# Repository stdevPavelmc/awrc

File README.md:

# Amateur Wireless Rotor Controller

An arduino based rotor controller connected via WiFi using the ESP8266 MCU

## Rationale

Why use cables when you have wifi around?

The hamlib project has a simple TCP daemon for abstract the rotor control, so we implemented the basic commands for that protocol and simulate a `rotctld` instance right on the rotor hardware; as today most of the softwares I use supports rotctld directly.

A web interface with position and simple commands is built on, I will improve it with time but this is low priority.

## How to compile

We use platformio, not the Arduino IDE, and main development is on linux (It must work on Windows/Mac), so you need Vscode/Codium and the Platformio addon.

By now I'm managing the dependencies as git submodules, so to install them you must do on the console this:

```sh
git clone https://github.com/stdevPavelmc/awrc.git
cd awrc
git submodule update
```

I will port them to platformio.ini deps in the future. Now just open the Platformio IDE and open the project and run. If you have internet plarformio will install the frameworks and tools for you.

## Hardware

There is a folder named `awrc-kicad` that has the project for board and schematics.

## This is a work in progress

Until labeled otherwise this project is an `alpha` code.

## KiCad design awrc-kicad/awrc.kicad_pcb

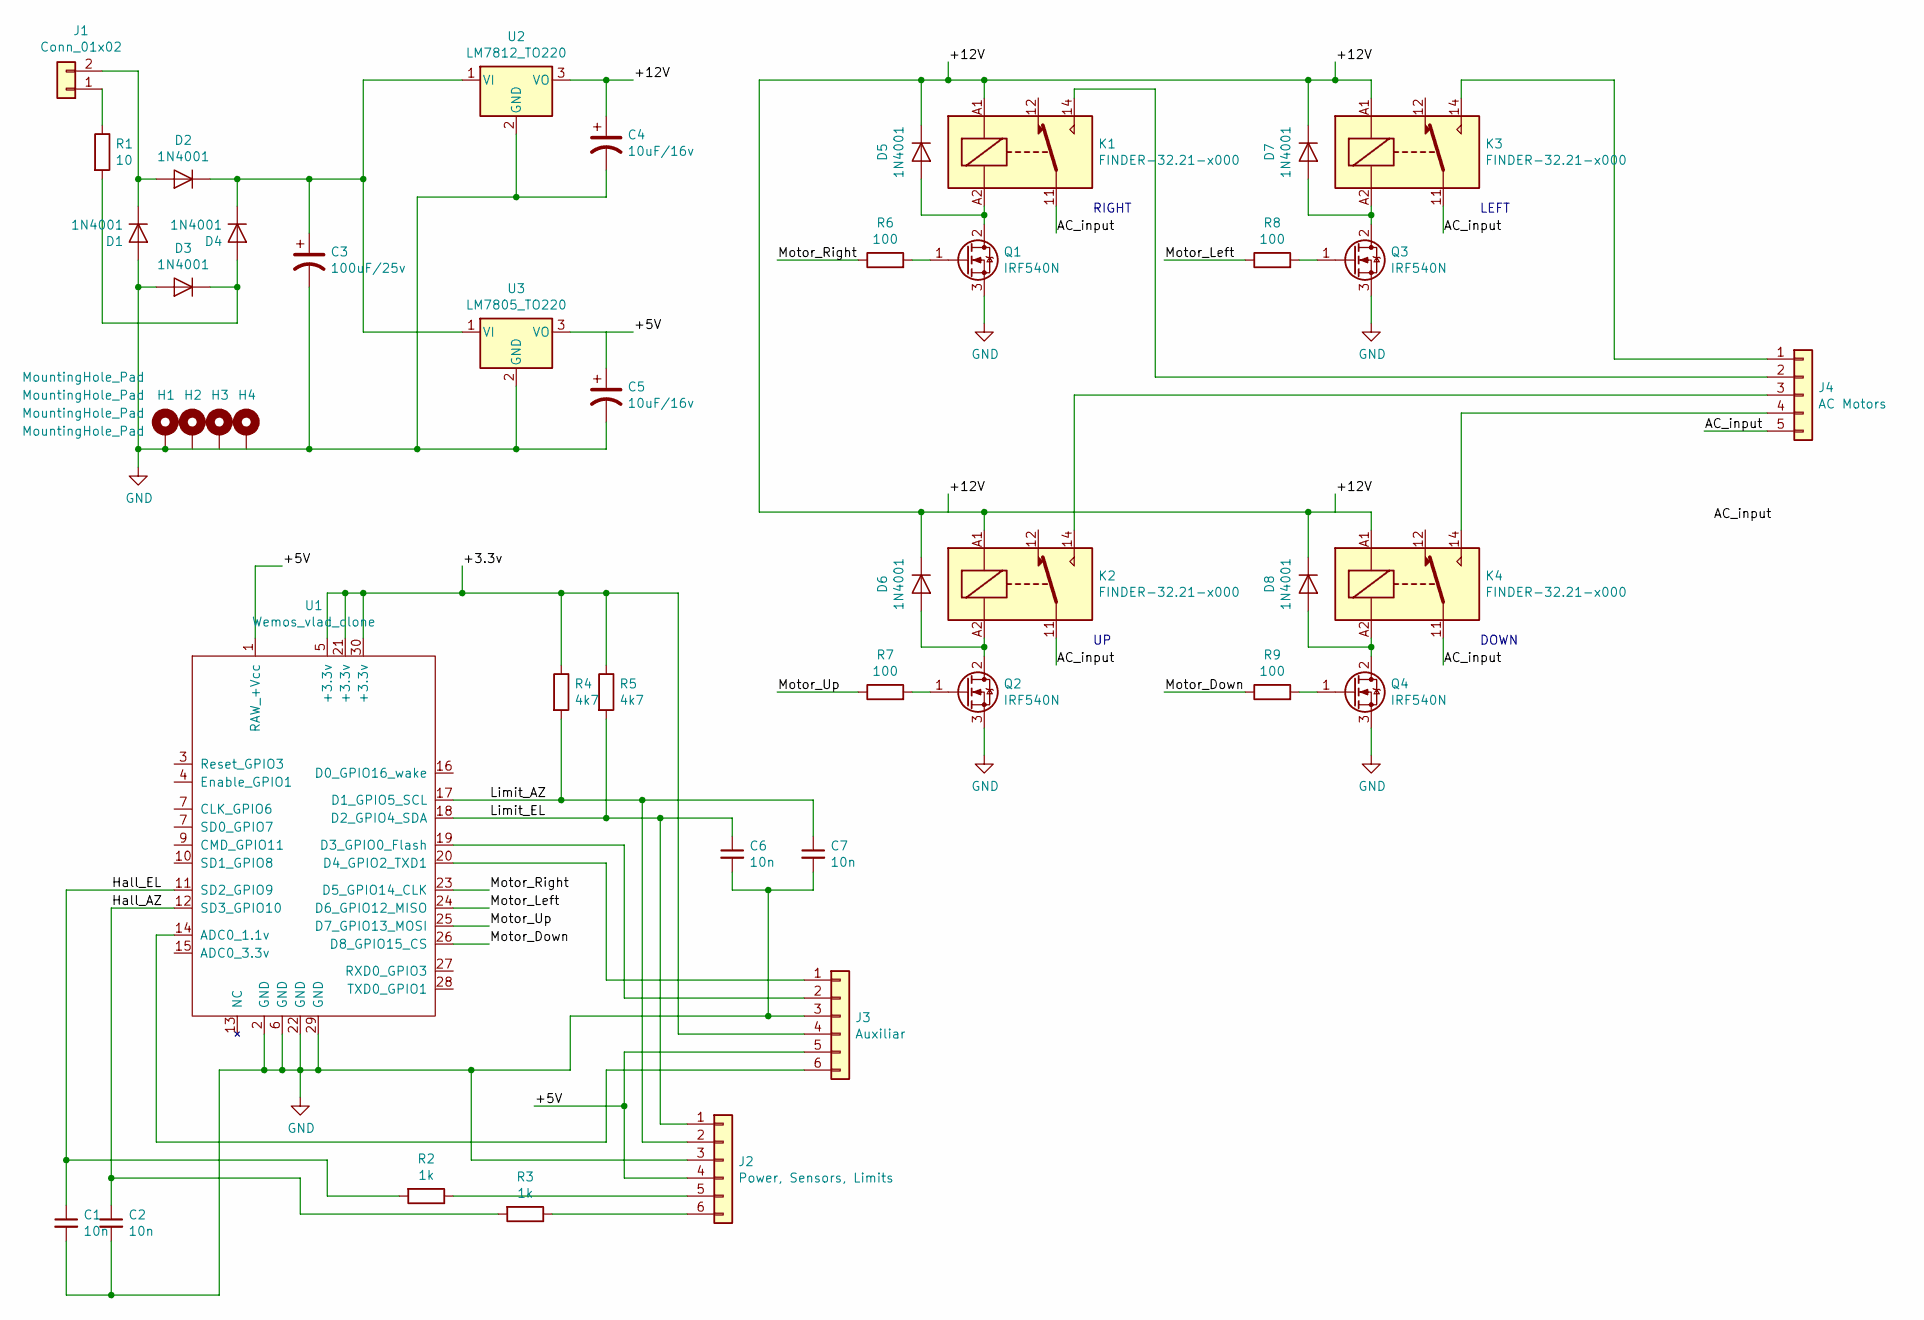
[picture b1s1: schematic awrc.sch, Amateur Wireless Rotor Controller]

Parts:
C1, C2, C6, C7: 10n; C_Disc_D7.5mm_W2.5mm_P5.00mm
C3: 100uF/25v; CP_Radial_D13.0mm_P5.00mm
C4, C5: 10uF/16v; CP_Radial_D10.0mm_P5.00mm
D1, D2, D3, D4, D5, D6, D7, D8: 1N4001; D_DO-41_SOD81_P10.16mm_Horizontal
H1, H2, H3, H4: MountingHole_Pad; MountingHole_3.2mm_M3_DIN965_Pad
J1: Conn_01x02; PinHeader_1x02_P2.54mm_Vertical
J2: Power, Sensors, Limits; PinHeader_1x06_P2.54mm_Vertical
J3: Auxiliar; PinHeader_1x06_P2.54mm_Vertical
J4: AC Motors; TerminalBlock_bornier-5_P5.08mm
K1, K2, K3, K4: FINDER-32.21-x000; Relay_THT_UPS_80H-1C-S
Q1, Q2, Q3, Q4: IRF540N; TO-220-3_Vertical
R1: 10; R_Axial_DIN0207_L6.3mm_D2.5mm_P10.16mm_Horizontal
R2, R3: 1k; R_Axial_DIN0207_L6.3mm_D2.5mm_P10.16mm_Horizontal
R4, R5: 4k7; R_Axial_DIN0207_L6.3mm_D2.5mm_P10.16mm_Horizontal
R6, R7, R8, R9: 100; R_Axial_DIN0207_L6.3mm_D2.5mm_P10.16mm_Horizontal
U1: Wemos_vlad_clone; Wemos_Clone
U2: LM7812_TO220; TO-220-3_Vertical
U3: LM7805_TO220; TO-220-3_Vertical

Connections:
/+3.3v: J3.4, R4.1, R5.1, U1.5 (+3.3v), U1.21 (+3.3v), U1.30 (+3.3v)
/+5V: C5.1, J2.4, J3.5, U1.1 (RAW_+Vcc), U3.3 (VO)
/+12V: C4.1, D5.1 (K), D6.1 (K), D7.1 (K), D8.1 (K), K1.A1, K2.A1, K3.A1, K4.A1, U2.3 (VO)
/AC_input: J4.5, K1.11, K2.11, K3.11, K4.11
/Hall_AZ: C2.1, R3.2, U1.12 (SD3_GPIO10)
/Hall_EL: C1.1, R2.2, U1.11 (SD2_GPIO9)
/Limit_AZ: C7.1, J2.2, R4.2, U1.17 (D1_GPIO5_SCL)
/Limit_EL: C6.1, J2.1, R5.2, U1.18 (D2_GPIO4_SDA)
/Motor_Down: R9.1, U1.26 (D8_GPIO15_CS)
/Motor_Left: R8.1, U1.24 (D6_GPIO12_MISO)
/Motor_Right: R6.1, U1.23 (D5_GPIO14_CLK)
/Motor_Up: R7.1, U1.25 (D7_GPIO13_MOSI)
GND: C1.2, C2.2, C3.2, C4.2, C5.2, C6.2, C7.2, D1.2 (A), D3.2 (A), H1.1, J2.3, J3.3, Q1.3 (S), Q2.3 (S), Q3.3 (S), Q4.3 (S), U1.2 (GND), U1.6 (GND), U1.22 (GND), U1.29 (GND), U2.2 (GND), U3.2 (GND)
unnamed: C3.1, D2.1 (K), D4.1 (K), U2.1 (VI), U3.1 (VI)
unnamed: D1.1 (K), D2.2 (A), J1.2
unnamed: D3.1 (K), D4.2 (A), R1.2
unnamed: D5.2 (A), K1.A2, Q1.2 (D)
unnamed: D6.2 (A), K2.A2, Q2.2 (D)
unnamed: D7.2 (A), K3.A2, Q3.2 (D)
unnamed: D8.2 (A), K4.A2, Q4.2 (D)
unnamed: J1.1, R1.1
unnamed: J2.5, R2.1
unnamed: J2.6, R3.1
unnamed: J3.1, U1.20 (D4_GPIO2_TXD1)
unnamed: J3.2, U1.19 (D3_GPIO0_Flash)
unnamed: J3.6, U1.14 (ADC0_1.1v)
unnamed: J4.1, K3.14
unnamed: J4.2, K1.14
unnamed: J4.3, K2.14
unnamed: J4.4, K4.14
unnamed: Q1.1 (G), R6.2
unnamed: Q2.1 (G), R7.2
unnamed: Q3.1 (G), R8.2
unnamed: Q4.1 (G), R9.2

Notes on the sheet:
RIGHT
LEFT
DOWN

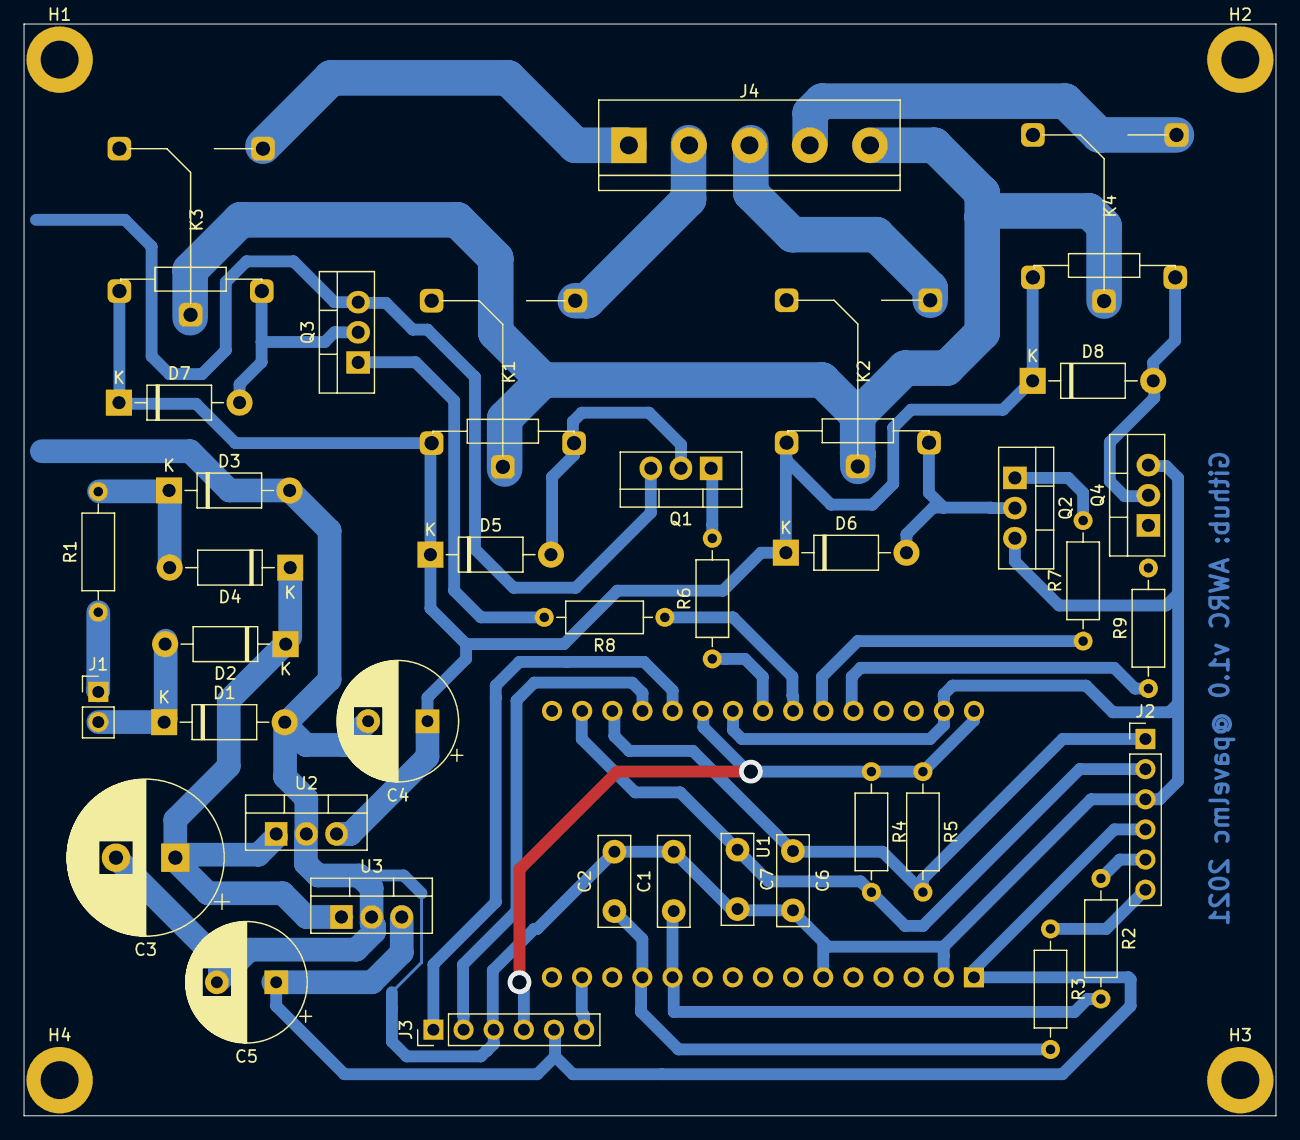
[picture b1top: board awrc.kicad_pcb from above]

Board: 2 copper layers, 105.5 x 92.0 mm, 43 parts (0 on the bottom side), 34 nets.

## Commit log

2021-09-22 first commit, pio folder structure
2021-09-22 Added the webserver and tcp libraries as submodules
2021-09-22 Add the wifi manager module
2021-09-22 platformio.ini
    Added monitor and ignore some conflicting libs
2021-09-22 Adding the first working copy of the main.cpp
2021-09-22 Add the config file
2021-09-22 Add a readme
2021-09-22 Add pinout and pin definitions
2021-09-23 huge update, a lot of functions but hitting a 'ISR not in iRAM' error and reboot, need to investigate that
2021-09-23 Modding the platformio.ini to complete OTA and memory partition
2021-09-23 Add debug flag
2021-09-23 Classic OTA, Debug, fix the TCP socket handling, etc...
2021-09-23 Remove the WiFiManager references.
2021-09-23 Add parking option and fix the removal of EleganOTA that broke the webserver
2021-09-23 fix full stop while parking and some others details
2021-09-23 First part of the calibration cycle, need to work on the eeprom saving and retrieving
2021-09-23 add crc and timer support for the eeprom feature
2021-09-23 Add config parameters to eeprom and autosave
2021-09-23 Add full eeprom support with autosave and struct save/retrieve
2021-09-27 Add Kicad files for the hardware
    This are the kicad files on revision 1.0
2021-09-29 Add the first code for the web server
2021-09-29 Add the FS data, dev version...
2021-10-01 Optimize JS, actions on buttons, etc.
2021-10-01 Add temp AP
2021-10-01 Useing enums to get track os state and using enum flags to trigger web commands
2021-10-01 Add basic status
2021-10-01 Comment some debugs, set the cmd to idle after the command ends, processing status
2021-10-01 Readme update
2021-10-03 Hardware change point, modify the boar or drop serial support instead od upd debug
2021-10-03 Modified esp8266 to release GPIO9/10 for hall pulses, details on docs
2021-10-08 Use default value from config when uncalibrated
2021-10-08 Add a 'c' command to show calibration results and change calibration command from 'c' to 'C' to match hamlib standard
2021-10-08 Fix the statuses to show on the web
2021-10-08 Move struct definitions to config and change minerror to MINERROR name
2021-10-08 First approximation to the use of the inertia of the rotation, must be tweaked on pactice... alpha code
2021-10-08 Add el ismoving code and improve precedence on need2move_az
2021-10-09 Port the inertia algorithm to elevation and fix the OTA update
2021-10-11 Fix max elevation
2021-10-11 Add web commands and Wifi level
2021-10-11 Add html/css glue to make buttons functions up/down/right/left/stop
2021-10-14 Web interface adapt to mobile devices
2021-10-18 Initial work on the set postition from the web, need cleanup
2021-11-28 Web interface changes, added bookmarks
2021-12-16 Add the dump_state command to the rotctld to get it compatible with rotctl type 2
2021-12-16 Add the doc of the dump_state command
